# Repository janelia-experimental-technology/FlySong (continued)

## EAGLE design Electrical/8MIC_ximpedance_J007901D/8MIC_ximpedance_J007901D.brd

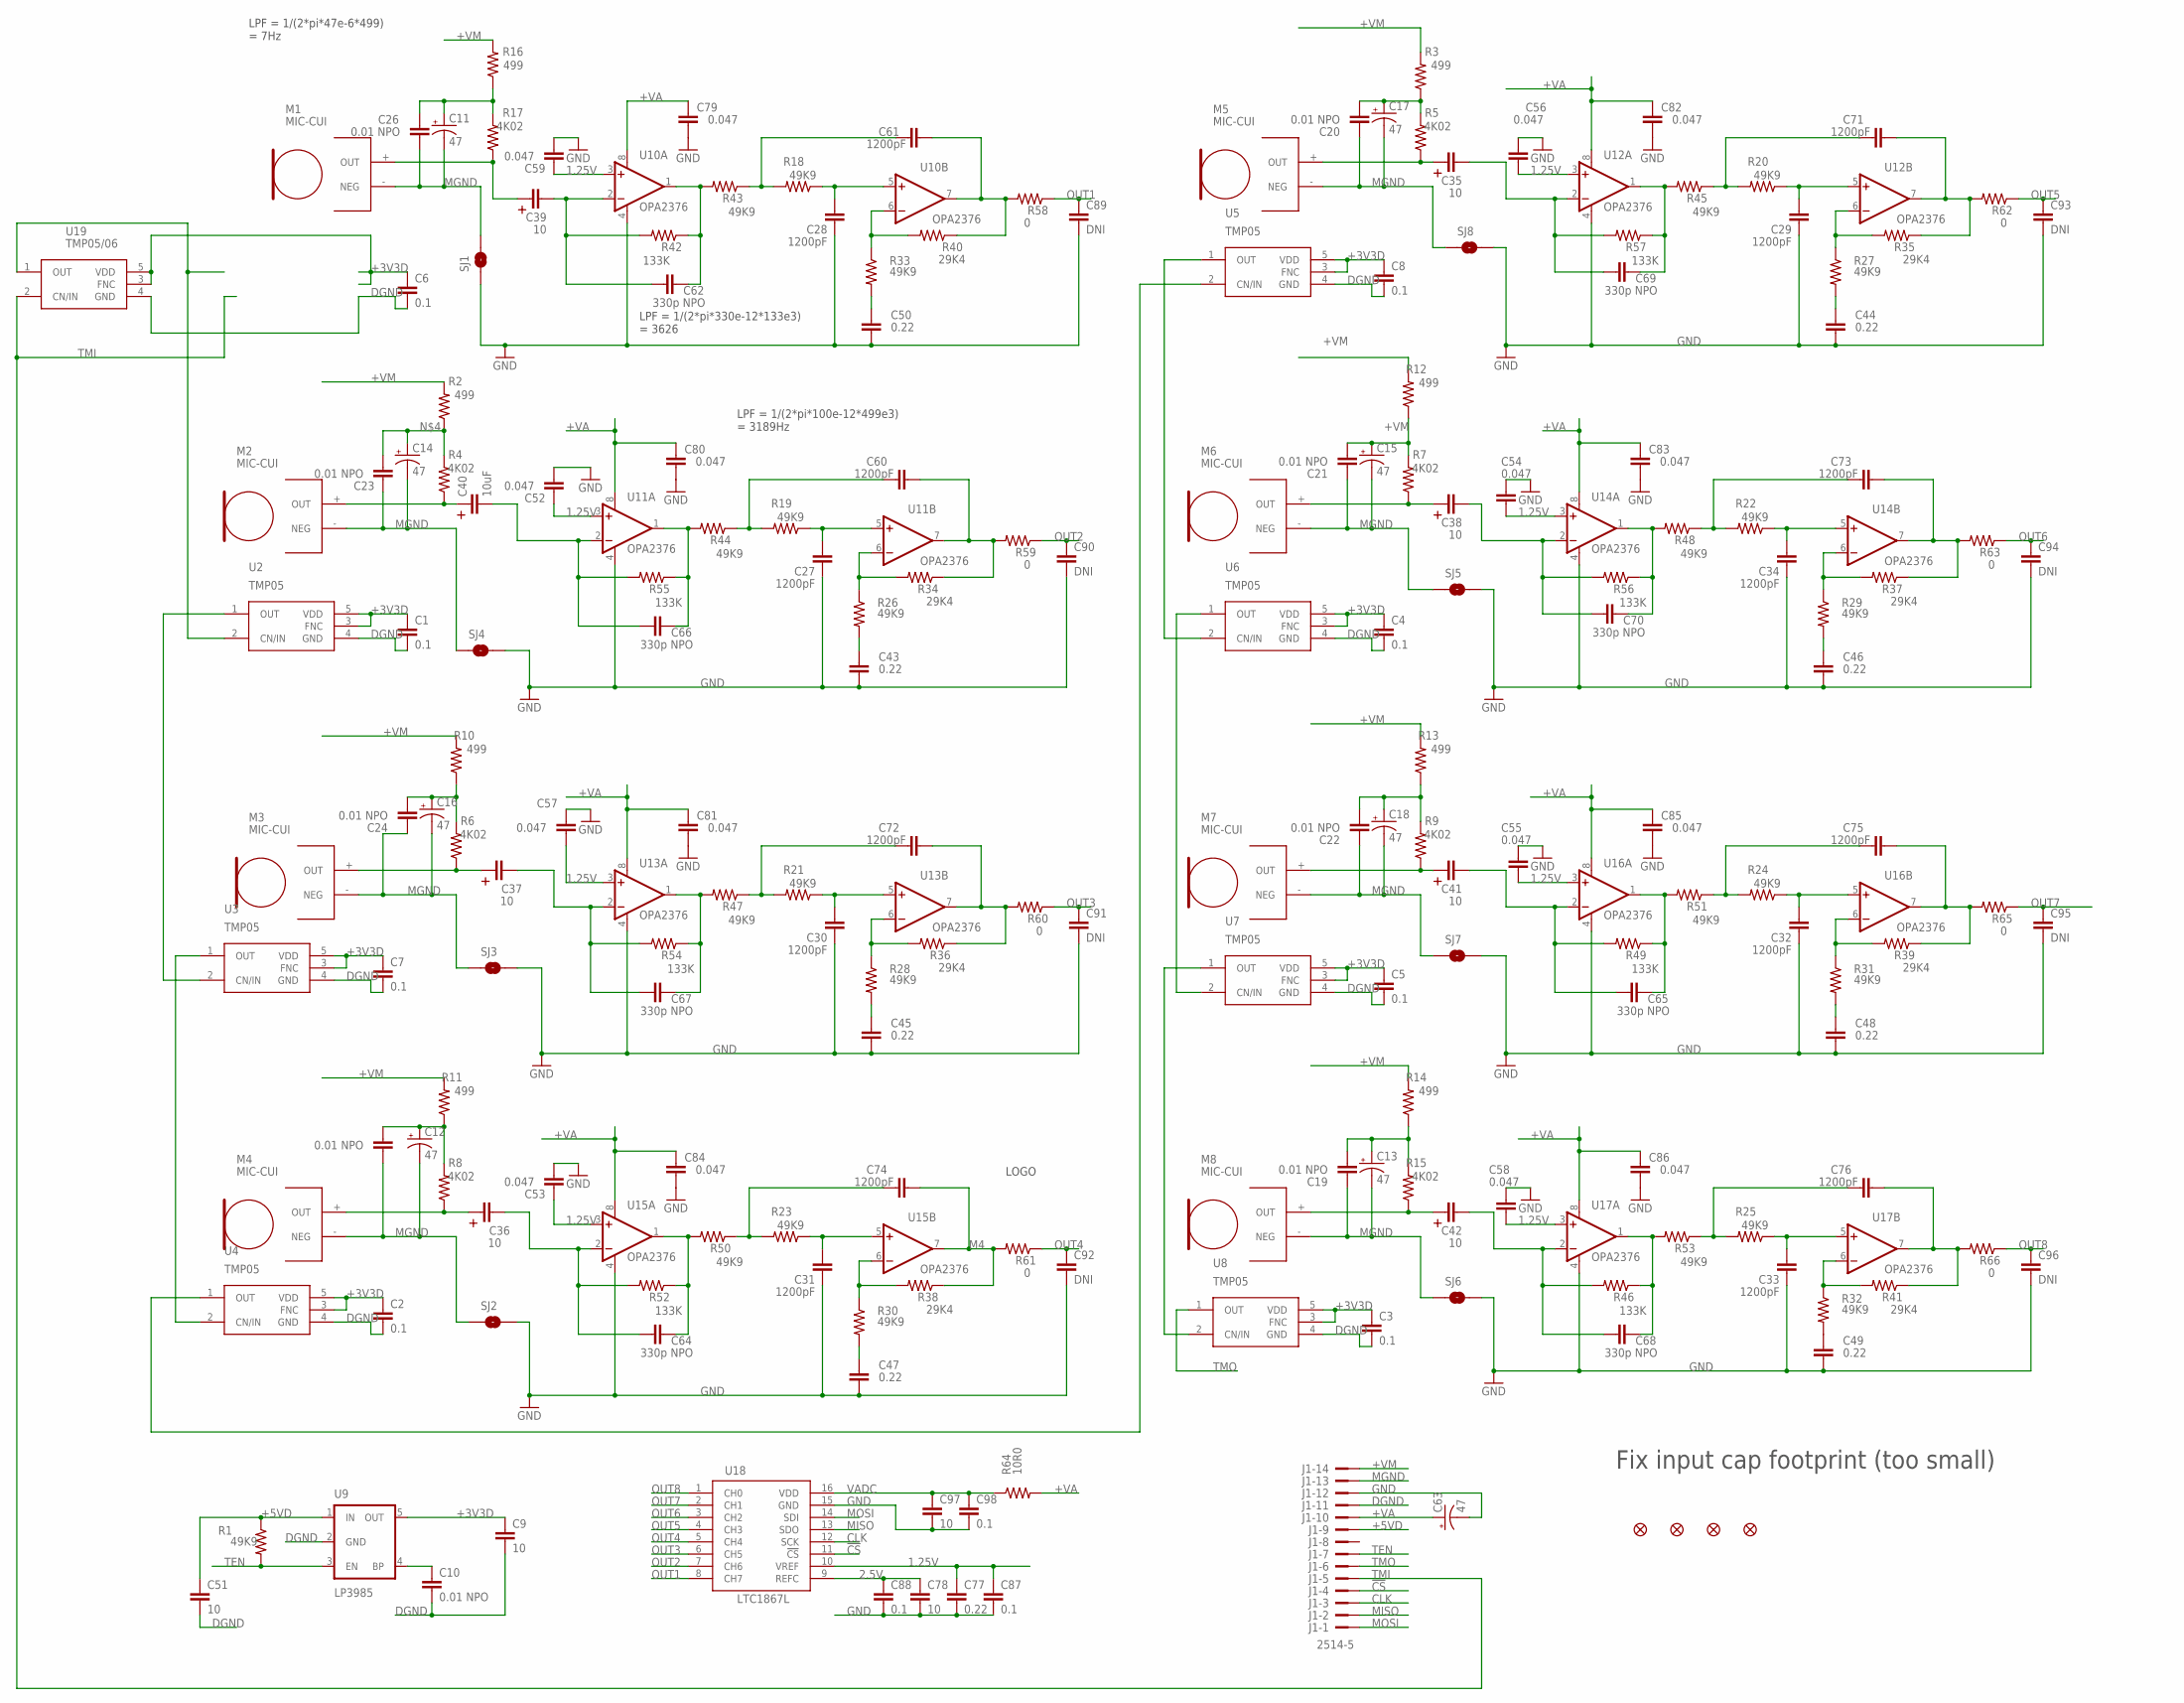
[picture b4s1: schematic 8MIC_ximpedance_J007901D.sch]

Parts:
C1, C2, C3, C4, C5, C6, C7, C8, C87, C88, C98: 0.1; 0805S
C9, C51, C78, C97: 10; 0805S
C10, C19, C20, C21, C22, C23, C24, C25, C26: 0.01 NPO; 0603S
C11, C12, C13, C14, C15, C16, C17, C18, C63: 47; EIA3216
C27, C28, C29, C30, C31, C32, C33, C34, C60, C61, C71, C72, C73, C74, C75, C76: 1200pF; 1206S
C35, C36, C37, C38, C39, C41, C42: 10; CAP_ELEC_A
C40: 10uF; CAP_ELEC_A
C43, C44, C45, C46, C47, C48, C49, C50: 0.22; 1206S
C52, C53, C54, C55, C56, C57, C58, C59, C79, C80, C81, C82, C83, C84, C85, C86: 0.047; 0805S
C62, C64, C65, C66, C67, C68, C69, C70: 330p NPO; 0805S
C77: 0.22; C1206
C89, C90, C91, C92, C93, C94, C95, C96: DNI; 0603S
J1: 2514-5; PAK100/2500-5-14
JP1, JP2, JP3, JP4: FIDUCIAL1.5X3; FIDUCIAL-1.5X3
M1, M2, M3, M4, M5, M6, M7, M8: MIC-CUI; CUI_EDGE
R1, R18, R19, R20, R21, R22, R23, R24, R25, R26, R27, R28, R29, R30, R31, R32, R33, R43, R44, R45, R47, R48, R50, R51, R53: 49K9; 0603S
R2, R3, R10, R11, R12, R13, R14, R16: 499; 0603S
R4, R5, R6, R7, R8, R9, R15, R17: 4K02; 0603S
R34, R35, R36, R37, R38, R39, R40, R41: 29K4; 0603S
R42, R46, R49, R52, R54, R55, R56, R57: 133K; 0603S
R58, R59, R60, R61, R62, R63, R65, R66: 0; 0603S
R64: 10R0; 0603S
SJ1, SJ2, SJ3, SJ4, SJ5, SJ6, SJ7, SJ8: SOLDERJUMPERTRACE; SJ_2S-TRACE
U2, U3, U4, U5, U6, U7, U8: TMP05; SOT23-5
U9: LP3985; SOT23-5
U10, U11, U12, U13, U14, U15, U16, U17: OPA2376; MSOP08
U18: LTC1867L; SSOP16
U19: TMP05/06; SOT-SC-5
U$1: JFRC-LOGOLOGO_OP; LOGO_BMP_OP

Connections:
1.25V: C52.2, C53.2, C54.2, C55.2, C56.2, C57.2, C58.2, C59.2, C77.1, C87.1, U10.3 (+IN), U11.3 (+IN), U12.3 (+IN), U13.3 (+IN), U14.3 (+IN), U15.3 (+IN), U16.3 (+IN), U17.3 (+IN), U18.10 (VREF)
2.5V: C78.1, C88.1, U18.9 (REFC)
!CS: J1.4, U18.11 (!CS)
+3V3D: C1.1, C2.1, C3.1, C4.1, C5.1, C6.1, C7.1, C8.1, C9.1, U2.3 (FNC), U2.5 (VDD), U3.3 (FNC), U3.5 (VDD), U4.3 (FNC), U4.5 (VDD), U5.3 (FNC), U5.5 (VDD), U6.3 (FNC), U6.5 (VDD), U7.3 (FNC), U7.5 (VDD), U8.3 (FNC), U8.5 (VDD), U9.5 (OUT), U19.3 (FNC), U19.5 (VDD)
+5VD: C51.1, J1.9, R1.1, U9.1 (IN)
+VA: C63.A (+), C79.2, C80.2, C81.2, C82.2, C83.2, C84.2, C85.2, C86.2, J1.10, R64.2, U10.8 (V+), U11.8 (V+), U12.8 (V+), U13.8 (V+), U14.8 (V+), U15.8 (V+), U16.8 (V+), U17.8 (V+)
+VM: J1.14, R2.2, R3.2, R10.2, R11.2, R12.2, R13.2, R14.2, R16.2
CLK: J1.3, U18.12 (SCK)
DGND: C1.2, C2.2, C3.2, C4.2, C5.2, C6.2, C7.2, C8.2, C9.2, C10.2, C51.2, J1.11, U2.4 (GND), U3.4 (GND), U4.4 (GND), U5.4 (GND), U6.4 (GND), U7.4 (GND), U8.4 (GND), U9.2 (GND), U19.4 (GND)
GND: C27.1, C28.1, C29.1, C30.1, C31.1, C32.1, C33.1, C34.1, C43.1, C44.1, C45.1, C46.1, C47.1, C48.1, C49.1, C50.1, C52.1, C53.1, C54.1, C55.1, C56.1, C57.1, C58.1, C59.1, C63.C (-), C77.2, C78.2, C79.1, C80.1, C81.1, C82.1, C83.1, C84.1, C85.1, C86.1, C87.2, C88.2, C89.2, C90.2, C91.2, C92.2, C93.2, C94.2, C95.2, C96.2, C97.2, C98.2, J1.12, SJ1.1, SJ2.2, SJ3.2, SJ4.2, SJ5.2, SJ6.2, SJ7.2, SJ8.2, U10.4 (V-), U11.4 (V-), U12.4 (V-), U13.4 (V-), U14.4 (V-), U15.4 (V-), U16.4 (V-), U17.4 (V-), U18.15 (GND)
M1: C61.1, R40.1, R58.2, U10.7 (OUT)
M2: C60.1, R34.1, R59.2, U11.7 (OUT)
M3: C72.1, R36.1, R60.2, U13.7 (OUT)
M4: C74.1, R38.1, R61.2, U15.7 (OUT)
M5: C71.1, R35.1, R62.2, U12.7 (OUT)
M6: C73.1, R37.1, R63.2, U14.7 (OUT)
M7: C75.1, R39.1, R65.2, U16.7 (OUT)
M8: C76.1, R41.1, R66.2, U17.7 (OUT)
MGND: C11.C (-), C12.C (-), C13.C (-), C14.C (-), C15.C (-), C16.C (-), C17.C (-), C18.C (-), C19.2, C20.2, C21.2, C22.2, C23.2, C24.2, C25.2, C26.2, J1.13, M1.- (NEG), M2.- (NEG), M3.- (NEG), M4.- (NEG), M5.- (NEG), M6.- (NEG), M7.- (NEG), M8.- (NEG), SJ1.2, SJ2.1, SJ3.1, SJ4.1, SJ5.1, SJ6.1, SJ7.1, SJ8.1
MIC4: C36.P (1P), M4.+ (OUT), R8.1
MISO: J1.2, U18.13 (SDO)
MOSI: J1.1, U18.14 (SDI)
unnamed: C39.P (1P), M1.+ (OUT), R17.1
unnamed: C39.M (2M), C62.2, R42.2, U10.2 (-IN)
unnamed: C40.P (1P), M2.+ (OUT), R4.1
unnamed: C14.A (+), C23.1, R2.1, R4.2
unnamed: C40.M (2M), C66.2, R55.2, U11.2 (-IN)
unnamed: C62.1, R42.1, R43.2, U10.1 (OUT)
unnamed: C11.A (+), C26.1, R16.1, R17.2
unnamed: C16.A (+), C24.1, R6.2, R10.1
unnamed: C61.2, R18.2, R43.1
unnamed: C28.2, R18.1, U10.5 (+IN)
unnamed: C17.A (+), C20.1, R3.1, R5.2
unnamed: C50.2, R33.2
unnamed: R33.1, R40.2, U10.6 (-IN)
unnamed: C66.1, R44.2, R55.1, U11.1 (OUT)
unnamed: C60.2, R19.2, R44.1
unnamed: C27.2, R19.1, U11.5 (+IN)
unnamed: C43.2, R26.2
unnamed: R26.1, R34.2, U11.6 (-IN)
unnamed: C37.P (1P), M3.+ (OUT), R6.1
unnamed: C12.A (+), C25.1, R8.2, R11.1
unnamed: C37.M (2M), C67.2, R54.2, U13.2 (-IN)
unnamed: C67.1, R47.2, R54.1, U13.1 (OUT)
unnamed: C72.2, R21.2, R47.1
unnamed: C30.2, R21.1, U13.5 (+IN)
unnamed: C45.2, R28.2
unnamed: R28.1, R36.2, U13.6 (-IN)
unnamed: C15.A (+), C21.1, R7.2, R12.1
unnamed: C18.A (+), C22.1, R9.2, R13.1
unnamed: C36.M (2M), C64.2, R52.2, U15.2 (-IN)
unnamed: C13.A (+), C19.1, R14.1, R15.2
unnamed: C64.1, R50.2, R52.1, U15.1 (OUT)
unnamed: C74.2, R23.2, R50.1
unnamed: C31.2, R23.1, U15.5 (+IN)
unnamed: C47.2, R30.2
unnamed: R30.1, R38.2, U15.6 (-IN)
unnamed: C35.M (2M), C69.2, R57.2, U12.2 (-IN)
unnamed: C69.1, R45.2, R57.1, U12.1 (OUT)
unnamed: C71.2, R20.2, R45.1
unnamed: C29.2, R20.1, U12.5 (+IN)
unnamed: C44.2, R27.2
unnamed: R27.1, R35.2, U12.6 (-IN)
unnamed: C38.P (1P), M6.+ (OUT), R7.1
unnamed: C38.M (2M), C70.2, R56.2, U14.2 (-IN)
unnamed: C70.1, R48.2, R56.1, U14.1 (OUT)
unnamed: C73.2, R22.2, R48.1
unnamed: C34.2, R22.1, U14.5 (+IN)
unnamed: C46.2, R29.2
unnamed: R29.1, R37.2, U14.6 (-IN)
unnamed: C41.P (1P), M7.+ (OUT), R9.1
unnamed: C41.M (2M), C65.2, R49.2, U16.2 (-IN)
unnamed: C65.1, R49.1, R51.2, U16.1 (OUT)
unnamed: C75.2, R24.2, R51.1
unnamed: C32.2, R24.1, U16.5 (+IN)
unnamed: C48.2, R31.2
unnamed: R31.1, R39.2, U16.6 (-IN)
unnamed: C42.P (1P), M8.+ (OUT), R15.1
unnamed: C42.M (2M), C68.2, R46.2, U17.2 (-IN)
unnamed: C68.1, R46.1, R53.2, U17.1 (OUT)
unnamed: C76.2, R25.2, R53.1
unnamed: C33.2, R25.1, U17.5 (+IN)
unnamed: C49.2, R32.2
unnamed: R32.1, R41.2, U17.6 (-IN)
unnamed: U2.2 (CN/IN), U19.1 (OUT)
unnamed: U2.1 (OUT), U3.2 (CN/IN)
unnamed: U3.1 (OUT), U4.2 (CN/IN)
unnamed: U4.1 (OUT), U5.2 (CN/IN)
unnamed: U5.1 (OUT), U6.2 (CN/IN)
unnamed: U6.1 (OUT), U7.2 (CN/IN)
unnamed: U7.1 (OUT), U8.2 (CN/IN)
unnamed: C10.1, U9.4 (BP)
unnamed: C35.P (1P), M5.+ (OUT), R5.1
OUT1: C89.1, R58.1, U18.8 (CH7)
OUT2: C90.1, R59.1, U18.7 (CH6)
OUT3: C91.1, R60.1, U18.6 (CH5)
OUT4: C92.1, R61.1, U18.5 (CH4)
OUT5: C93.1, R62.1, U18.4 (CH3)
OUT6: C94.1, R63.1, U18.3 (CH2)
OUT7: C95.1, R65.1, U18.2 (CH1)
OUT8: C96.1, R66.1, U18.1 (CH0)
TEN: J1.7, R1.2, U9.3 (EN)
TMI: J1.5, U19.2 (CN/IN)
TMO: J1.6, U8.1 (OUT)
VADC: C97.1, C98.1, R64.1, U18.16 (VDD)

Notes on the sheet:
LPF = 1/(2*pi*47e-6*499) = 7Hz
LPF = 1/(2*pi*100e-12*499e3) = 3189Hz
LPF = 1/(2*pi*330e-12*133e3) = 3626
Fix input cap footprint (too small)

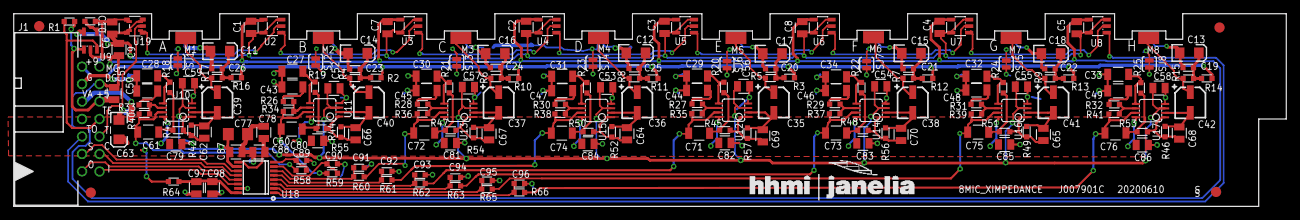
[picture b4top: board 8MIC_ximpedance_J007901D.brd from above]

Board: 2 copper layers, 185.0 x 28.0 mm, 204 parts (0 on the bottom side), 105 nets.

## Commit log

2023-11-08 Update README.md
    add description
2023-11-08 Add files via upload
    Add in executables
2023-11-08 Rename UnZIP to root directory to Place in Root Directory
2023-11-08 Add files via upload
    Change dir to FlySongExecutables
2023-11-08 Add files via upload
    Added Eagle Files and Gerbers
2023-11-08 Added Mechanical Files
2023-11-08 Added full parts list
2023-11-13 Add Source Code
    Added FlySong and FPGA source code
2023-11-13 Create LICENSE.txt
    Add Janella licence file
2023-11-13 Delete FlySongExecutables directory
    Redundant directory
2023-11-13 rename directory
    from FlySong to FlySongExecutablesAndRunFiles
2023-11-13 Edited 96ch sample file
    Made each name unique and indicative of the cell it is in
2024-01-04 Add Install Files for Camera Software
2024-01-10 Add link to paper
2024-05-21 RGB Control updates
    Add RGB serial control connector to backplane
    Add RGB serial control to FPGA firmware and FlySong software
2024-05-21 Update runtime files and add miniFlySong
    Updated run time files to run the version with serial RGB control
    Added miniFlySong. This design utilizes a small board with a Teensy 4.0 to run FlySong on a single 8 channel board, without the 12 slot Backplane board, Useful for small experiments. Uses a special v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
2024-05-23 add miniFlySong and rig photos
2024-05-31 Create FlySongRGBMirrors.dxf
    Laser cut file for FlySong mirrors used with RGB lighting
2024-05-31 Add mechanical parts to FlySong RGB
2024-06-03 Add 35mm arena to Fly Song Rig
    35 mm arena uses 7 microphones to record flies in a 35 mm diameter arena. It plugs into the FlySong backplane.
2024-07-17 Update BOMs and boards, add miniFlySong photo
2024-08-19 Backplane BOM, FPGA RGB control error
    Backplane BOM had incorrect parts for the BNC and Battery connector
    Fixed spelling error in Eagle note
    There were errors when the backplane controlled an RGB display via serial control. The serial circular buffer was not being filled correctly at wrap around. Code was changed so that the buffer was fi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
2024-10-15 Updates and corrections
    Updated BOM with correct quantities
    Latest FPGA file
    Updated 3D print and laser cut files
2025-01-11 Update BOM, add 3D pdf of rig, add load cover laser cut file fro 12x12 sheet
2025-01-28 update print files and BOM
    Change diffuser to 1/8" not 1/16"
2025-01-30 Update silkscreen to reflect board rev D and correct rev date, rename U19 to U1
